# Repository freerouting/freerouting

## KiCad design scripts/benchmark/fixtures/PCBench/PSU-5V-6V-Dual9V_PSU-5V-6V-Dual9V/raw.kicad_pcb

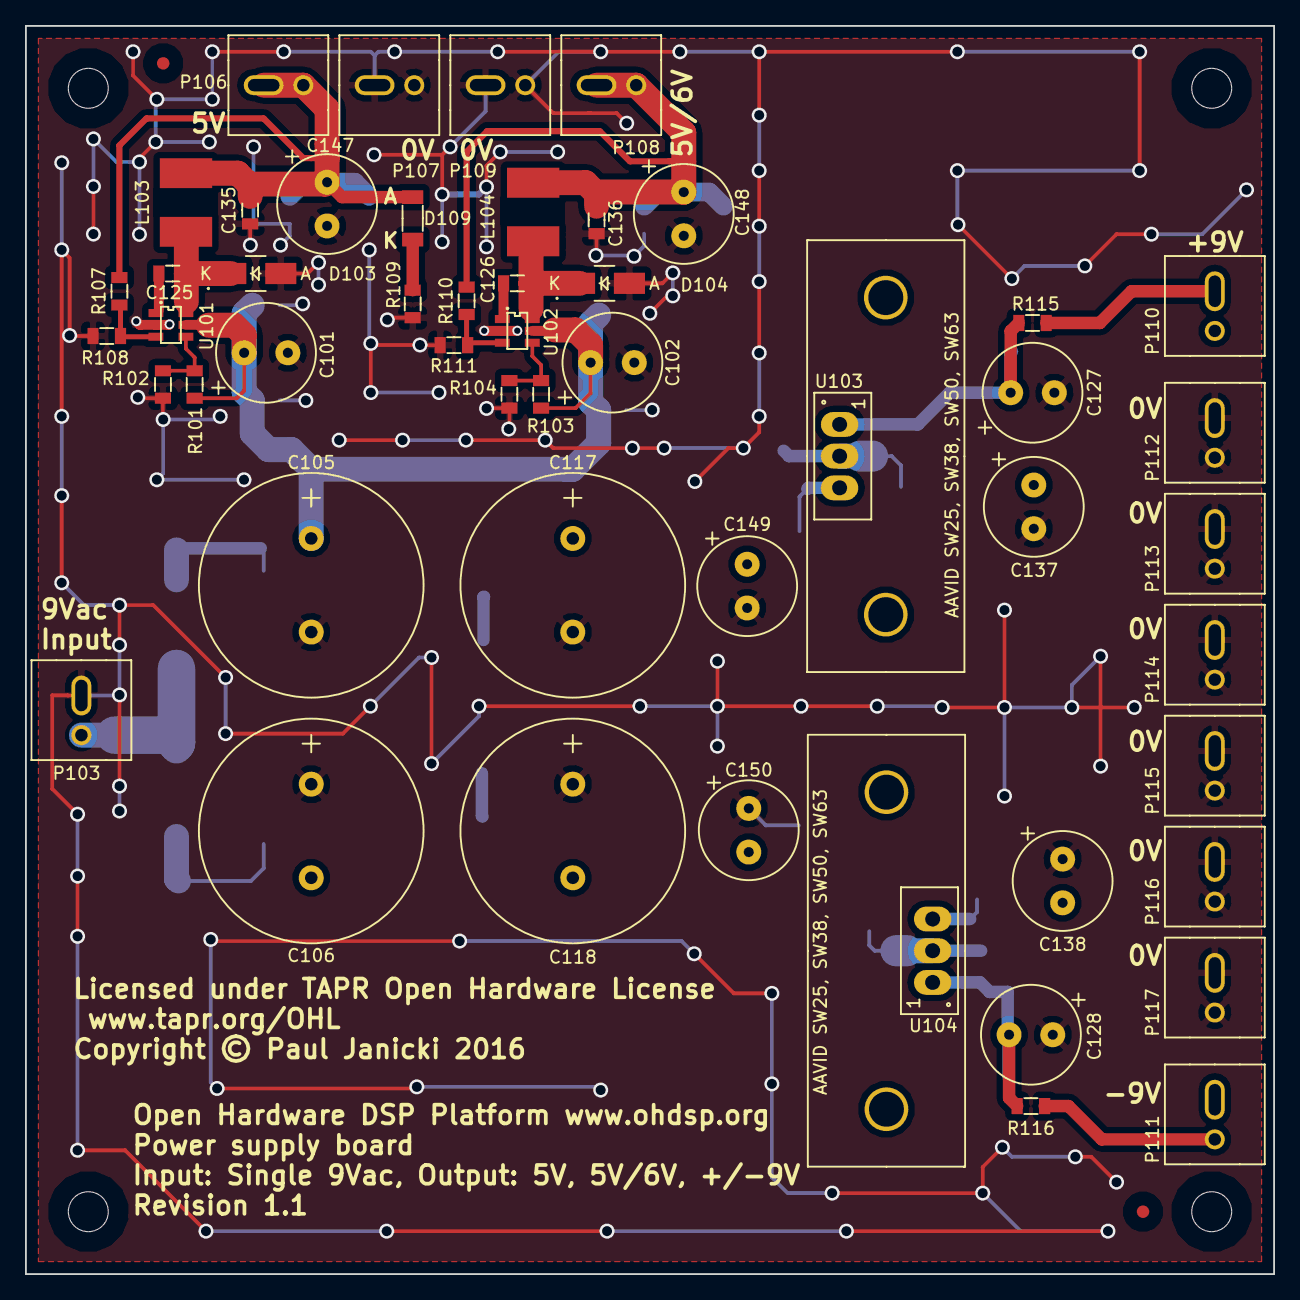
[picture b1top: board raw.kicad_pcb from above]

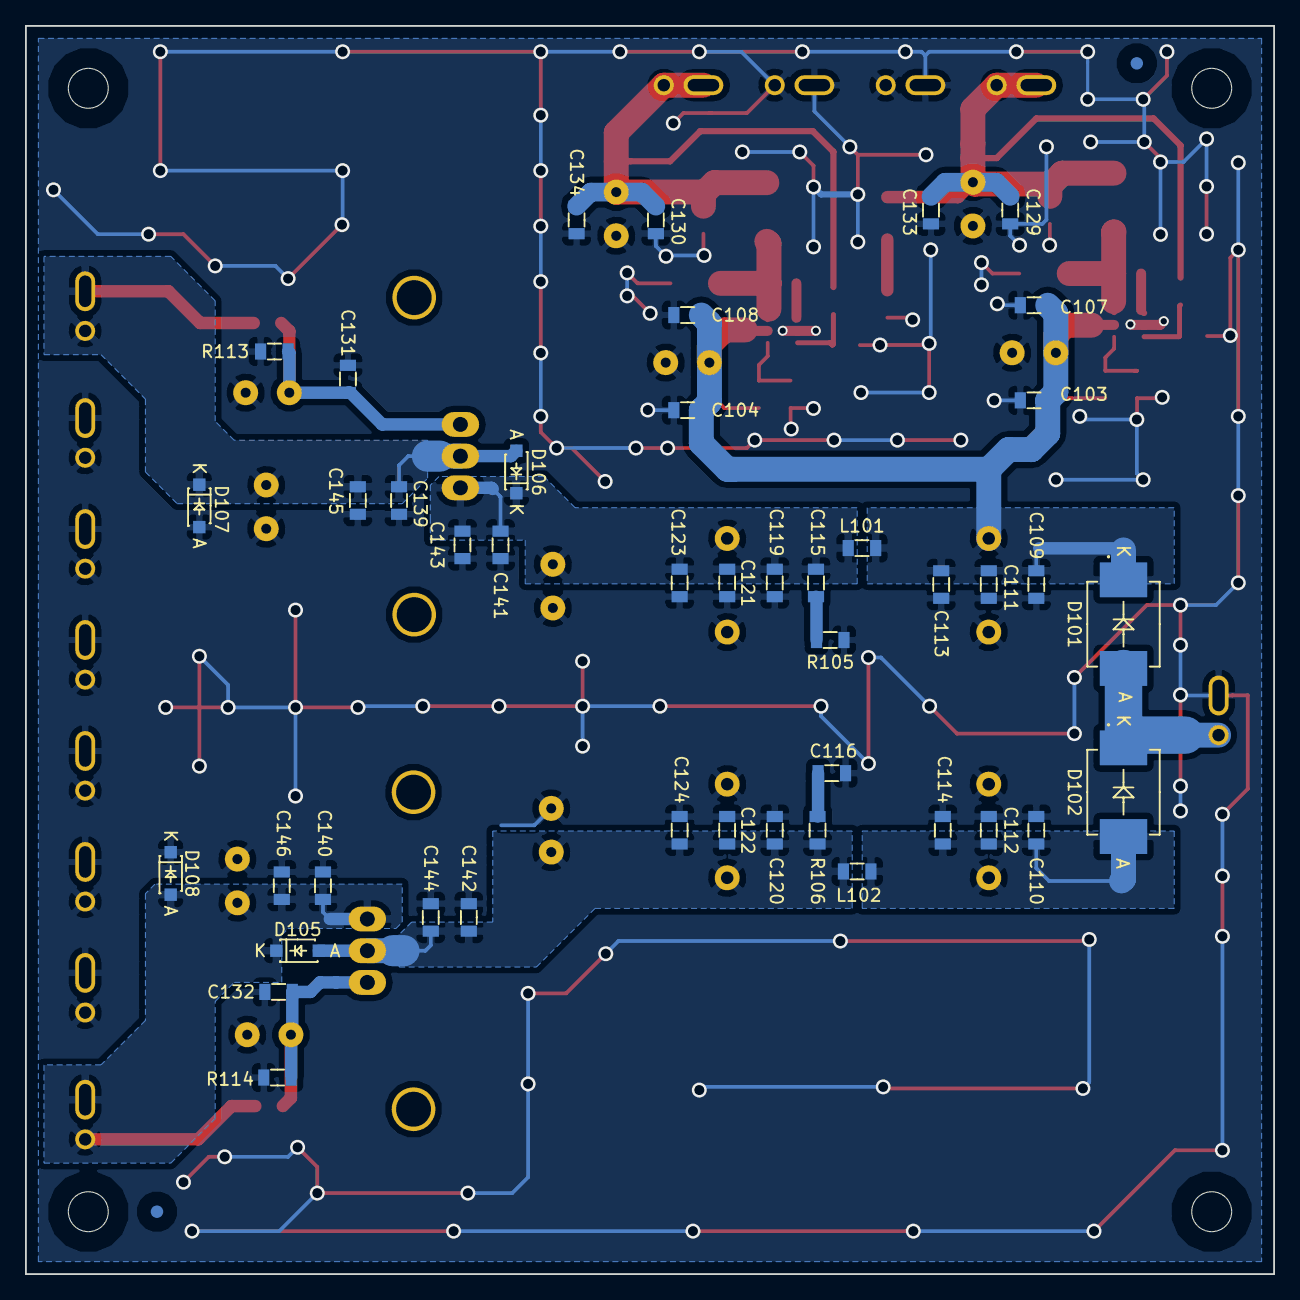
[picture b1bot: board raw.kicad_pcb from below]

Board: 2 copper layers, 100.0 x 100.0 mm, 103 parts (46 on the bottom side), 23 nets.

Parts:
C101, C102, C127, C128, C137, C138, C147, C148, C149, C150: 220u; CAP-TH-D8mmP3.5mm
C103, C104, C109, C110, C119, C120, C129, C130, C133, C134, C141, C142, C145, C146: 22u; SMD-0805
C105, C106, C117, C118: 2200u; CAP-TH-D18mmP7.5mm
C107, C108, C111, C112, C121, C122, C131, C132, C135, C136, C139, C140, C143, C144: 100n; SMD-0805
C113, C114, C123, C124, C125, C126: 10n; SMD-0805
C115, C116: 100p; SMD-0805
D101, D102: ES3D; DIODE-SMC
D103, D104: B240A; DIODE-SMA
D105, D106, D107, D108: SS14L; DIODE-SOD-123
D109: Green LED 1206; SMD-1206
FID1, FID2, FID3, FID4: MNT_HOLE; FID-1MM-3MM
L101, L102: 600R@100MHz; SMD-0805
L103, L104: TYS50406R8M-10; IND-TYS5040-HS
MNT1, MNT2, MNT3, MNT4: MNT_HOLE; MNT_HOLE_3.2mm
P103, P106, P107, P108, P109, P110, P111, P112, P113, P114, P115, P116, P117: CONN_2x1; CONN-2WAY-2.54mm-3.81mm-SPACING
R101, R103: 475k; SMD-0805
R102, R104: 100k; SMD-0805
R105, R106: 47; SMD-0805
R107: 53k6; SMD-0805
R108, R111: 10k; SMD-0805
R109: 470; SMD-0805
R110: 66k5; SMD-0805
R113, R114: 750; SMD-0805
R115, R116: 120; SMD-0805
U101, U102: ADP2301AUJZ; IC-SOT23-6
U103: LM317; IC-TO220-HS-SW25-2G
U104: LM337; IC-TO220-HS-SW25-2G

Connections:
+5V: C129.1, C133.1, C135.1, C147.1, D109.1, L103.2, P106.1, P106.2, R107.1
GNDA: C101.2, C102.2, C103.2, C104.2, C105.2, C106.1, C107.2, C108.2, C109.2, C110.1, C111.2, C112.1, C113.2, C114.1, C116.1, C117.2, C118.1, C119.2, C120.1, C121.2, C122.1, C123.2, C124.1, C127.2, C128.1, C129.2, C130.2, C131.2, C132.1, C133.2, C134.2, C135.2, C136.2, C137.2, C138.1, C139.2, C140.1, C141.2, C142.1, C143.2, C144.1, C145.2, C146.1, C147.2, C148.2, C149.2, C150.1, D103.1, D104.1, D107.1, D108.2, P103.2, P107.1, P107.2, P109.1, P109.2, P112.1, P112.2, P113.1, P113.2, P114.1, P114.2, P115.1, P115.2, P116.1, P116.2, P117.1, P117.2, R102.2, R104.2, R105.2, R108.1, R109.1, R111.1, R113.1, R114.2, U101.2, U102.2
unnamed: C106.2, C110.2, C112.2, C114.2, D102.1, L102.1
unnamed: C115.1, C117.1, C119.1, C121.1, C123.1, C141.1, C143.1, C149.1, D106.2, L101.2, U103.3
unnamed: C115.2, R105.1
unnamed: C116.2, R106.1
unnamed: C118.2, C120.2, C122.2, C124.2, C142.2, C144.2, C150.2, D105.1, L102.2, R106.2, U104.2
unnamed: C125.1, D103.2, L103.1, U101.6
unnamed: C125.2, U101.1
unnamed: C126.1, D104.2, L104.1, U102.6
unnamed: C126.2, U102.1
unnamed: C127.1, C131.1, R113.2, R115.1, U103.1
unnamed: C128.2, C132.2, R114.1, R116.1, U104.1
unnamed: C130.1, C134.1, C136.1, C148.1, L104.2, P108.1, P108.2, R110.1
unnamed: C137.1, C139.1, C145.1, D106.1, D107.2, P110.1, P110.2, R115.2, U103.2
unnamed: C138.2, C140.2, C146.2, D105.2, D108.1, P111.1, P111.2, R116.2, U104.3
unnamed: D101.1, D102.2, P103.1
unnamed: D109.2, R109.2
unnamed: R101.1, R102.1, U101.4
unnamed: R103.1, R104.1, U102.4
unnamed: R107.2, R108.2, U101.3
unnamed: R110.2, R111.2, U102.3
VCC: C101.1, C102.1, C103.1, C104.1, C105.1, C107.1, C108.1, C109.1, C111.1, C113.1, D101.2, L101.1, R101.2, R103.2, U101.5, U102.5

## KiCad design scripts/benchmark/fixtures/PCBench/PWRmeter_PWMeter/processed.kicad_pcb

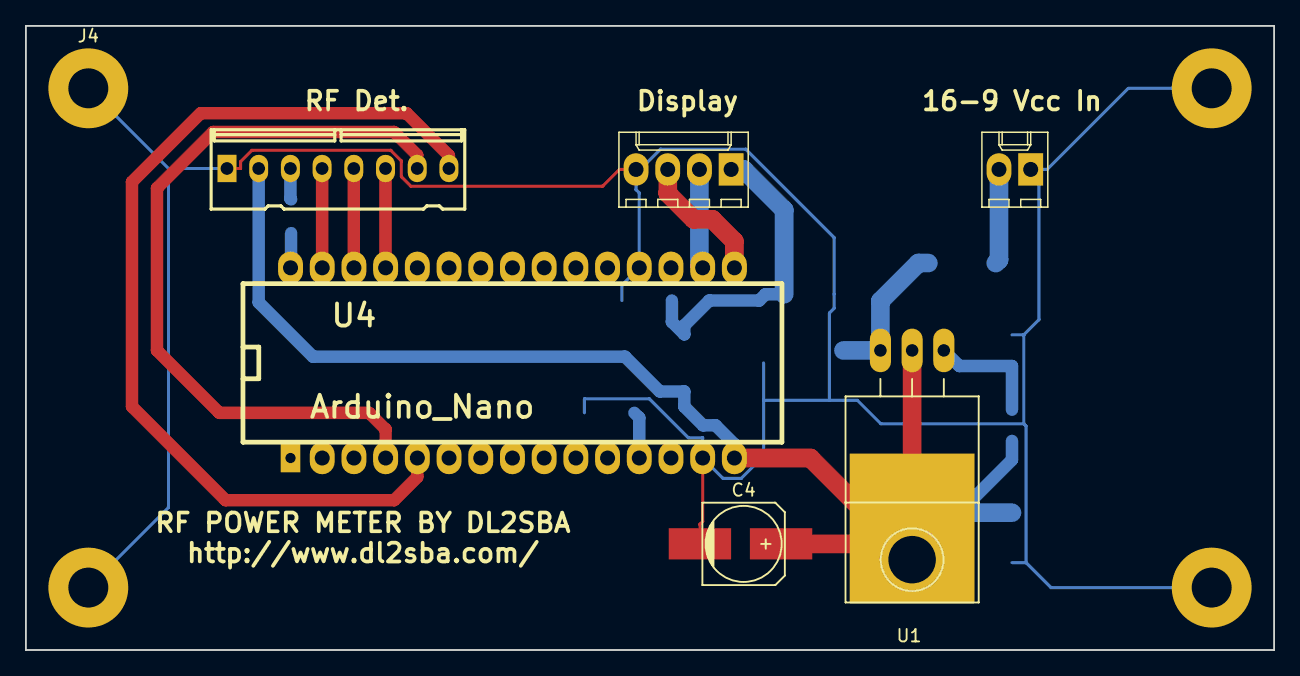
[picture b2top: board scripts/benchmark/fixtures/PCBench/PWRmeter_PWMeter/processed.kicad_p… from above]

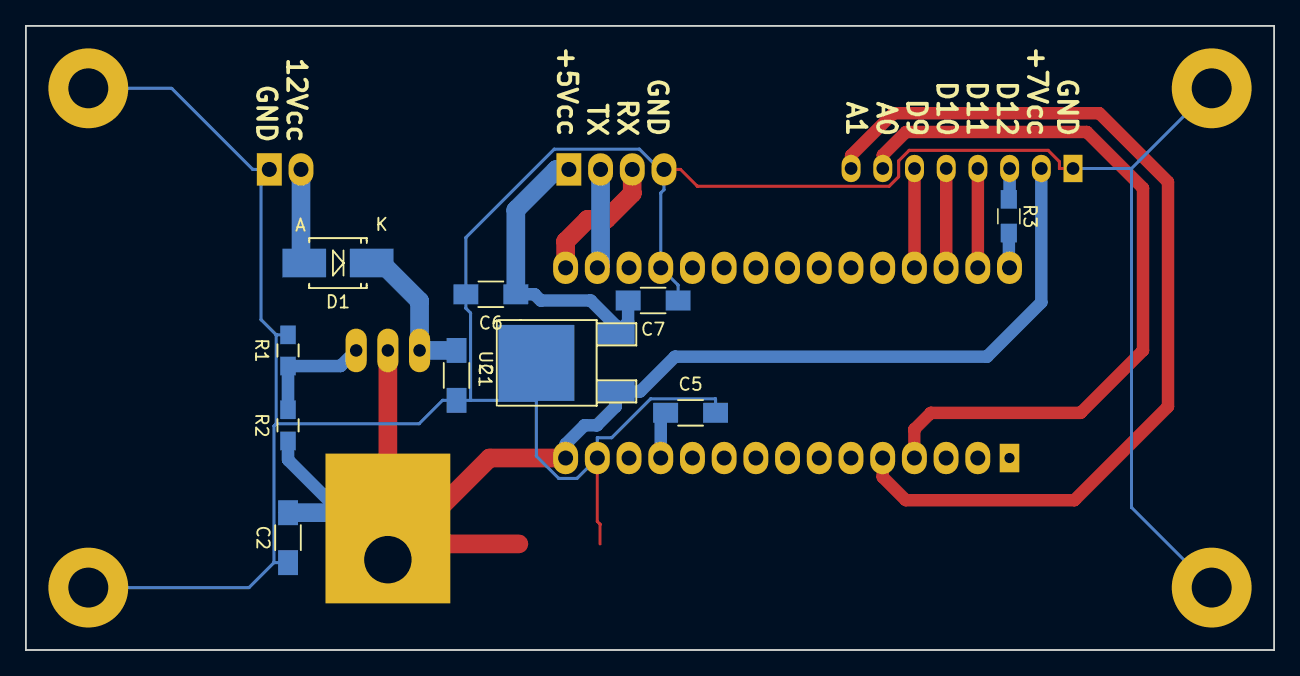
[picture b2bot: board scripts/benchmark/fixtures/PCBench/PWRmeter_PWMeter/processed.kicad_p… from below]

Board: 2 copper layers, 100.0 x 50.0 mm, 20 parts (10 on the bottom side), 16 nets.

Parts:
C1, C2, C5, C6, C7: 100n; C_1206_HandSoldering
C4: 1500uF; c_elec_6.3x7.7
D1: D_Schottky; SMB_Handsoldering
J1, J2, J3, J4: TEST_1P; MountingHole_3.2mm_M3_Pad
J5: CONN_01X08; kk100_22-23-2081
P1: 16/9V in; Molex_KK-6410-02_02x2.54mm_Straight
P5: Display; Molex_KK-6410-04_04x2.54mm_Straight
R1: 110; C_0805_HandSoldering
R2: 240; C_0805_HandSoldering
R3: 100R; R_0805_HandSoldering
U1: LM317T; TO-220_Neutral123_Horizontal_LargePads
U2: MC78M05CDT; TO-252-2Lead
U4: Arduino_Nano; arduino_nano

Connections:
+5C: C6.1, C7.2, P5.1, U2.3
+8V: C2.1, C4.1, J5.2, R2.1, U1.2, U2.1, U4.15
+12V: D1.2, P1.2
GND: C1.2, C2.2, C4.2, C5.2, C6.2, C7.1, J1.1, J2.1, J3.1, J4.1, J5.1, P1.1, P5.4, R1.2, U2.2, U4.14, U4.19
unnamed: C1.1, D1.1, U1.3
unnamed: C5.1, U4.12
unnamed: J5.3, R3.1
unnamed: J5.4, U4.29
unnamed: J5.5, U4.28
unnamed: J5.6, U4.27
unnamed: J5.7, U4.4
unnamed: J5.8, U4.5
unnamed: P5.2, U4.17
unnamed: P5.3, U4.16
unnamed: R1.1, R2.2, U1.1
unnamed: R3.2, U4.30

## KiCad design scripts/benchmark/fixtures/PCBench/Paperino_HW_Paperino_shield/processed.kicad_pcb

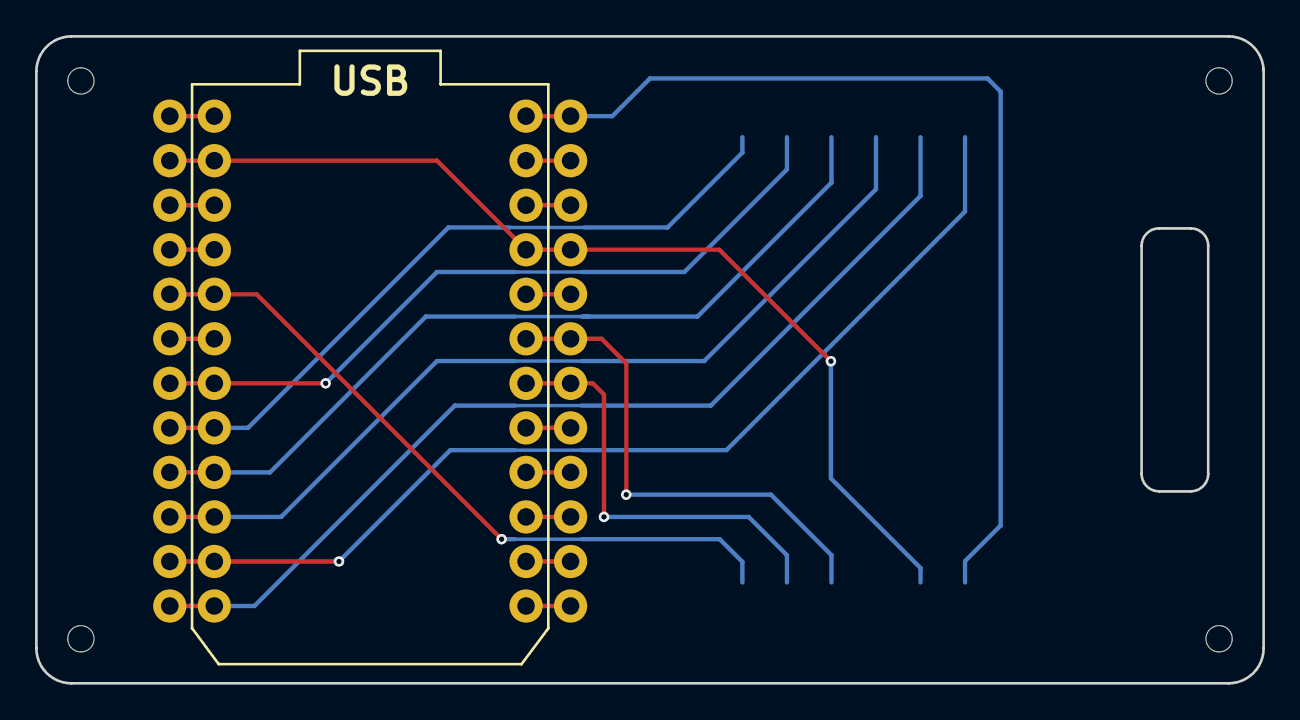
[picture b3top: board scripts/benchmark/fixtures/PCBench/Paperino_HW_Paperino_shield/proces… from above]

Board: 2 copper layers, 70.0 x 36.9 mm, 6 parts (1 on the bottom side), 11 nets.

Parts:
A1: Photon; photon_headers
A2: paperino_module
M1, M2, M3, M4: Mounting_hole; mounting_hole_1.5

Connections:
+3V3: A1.24, A2.1
/INT1: A1.5, A2.6
/INT2: A1.18, A2.5
/SPI_CLK: A1.9, A2.9
/SPI_CS1: A1.10, A2.10
/SPI_CS2: A1.19, A2.4
/SPI_MISO: A1.8, A2.7
/SPI_MOSI: A1.7, A2.8
/~BUSY: A1.11, A2.12
/~RST: A1.12, A2.11
GND: A1.2, A1.21, A2.2

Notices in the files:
scripts/benchmark/fixtures/PCBench/PSU-5V-6V-Dual9V_PSU-5V-6V-Dual9V/raw.kicad_pcb:
Licensed under the TAPR Open Hardware License (www.tapr.org/OHL). This documentation
Copyright Paul Janicki 2016
Licensed under TAPR Open Hardware License
Copyright © Paul Janicki 2016
scripts/benchmark/fixtures/PCBench/Paperino_HW_Paperino_shield/processed.kicad_pcb:
licensed under CC-BY 4.0
